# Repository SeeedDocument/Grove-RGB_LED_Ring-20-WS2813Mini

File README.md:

# Grove-RGB_LED_Ring-20-WS2813Mini

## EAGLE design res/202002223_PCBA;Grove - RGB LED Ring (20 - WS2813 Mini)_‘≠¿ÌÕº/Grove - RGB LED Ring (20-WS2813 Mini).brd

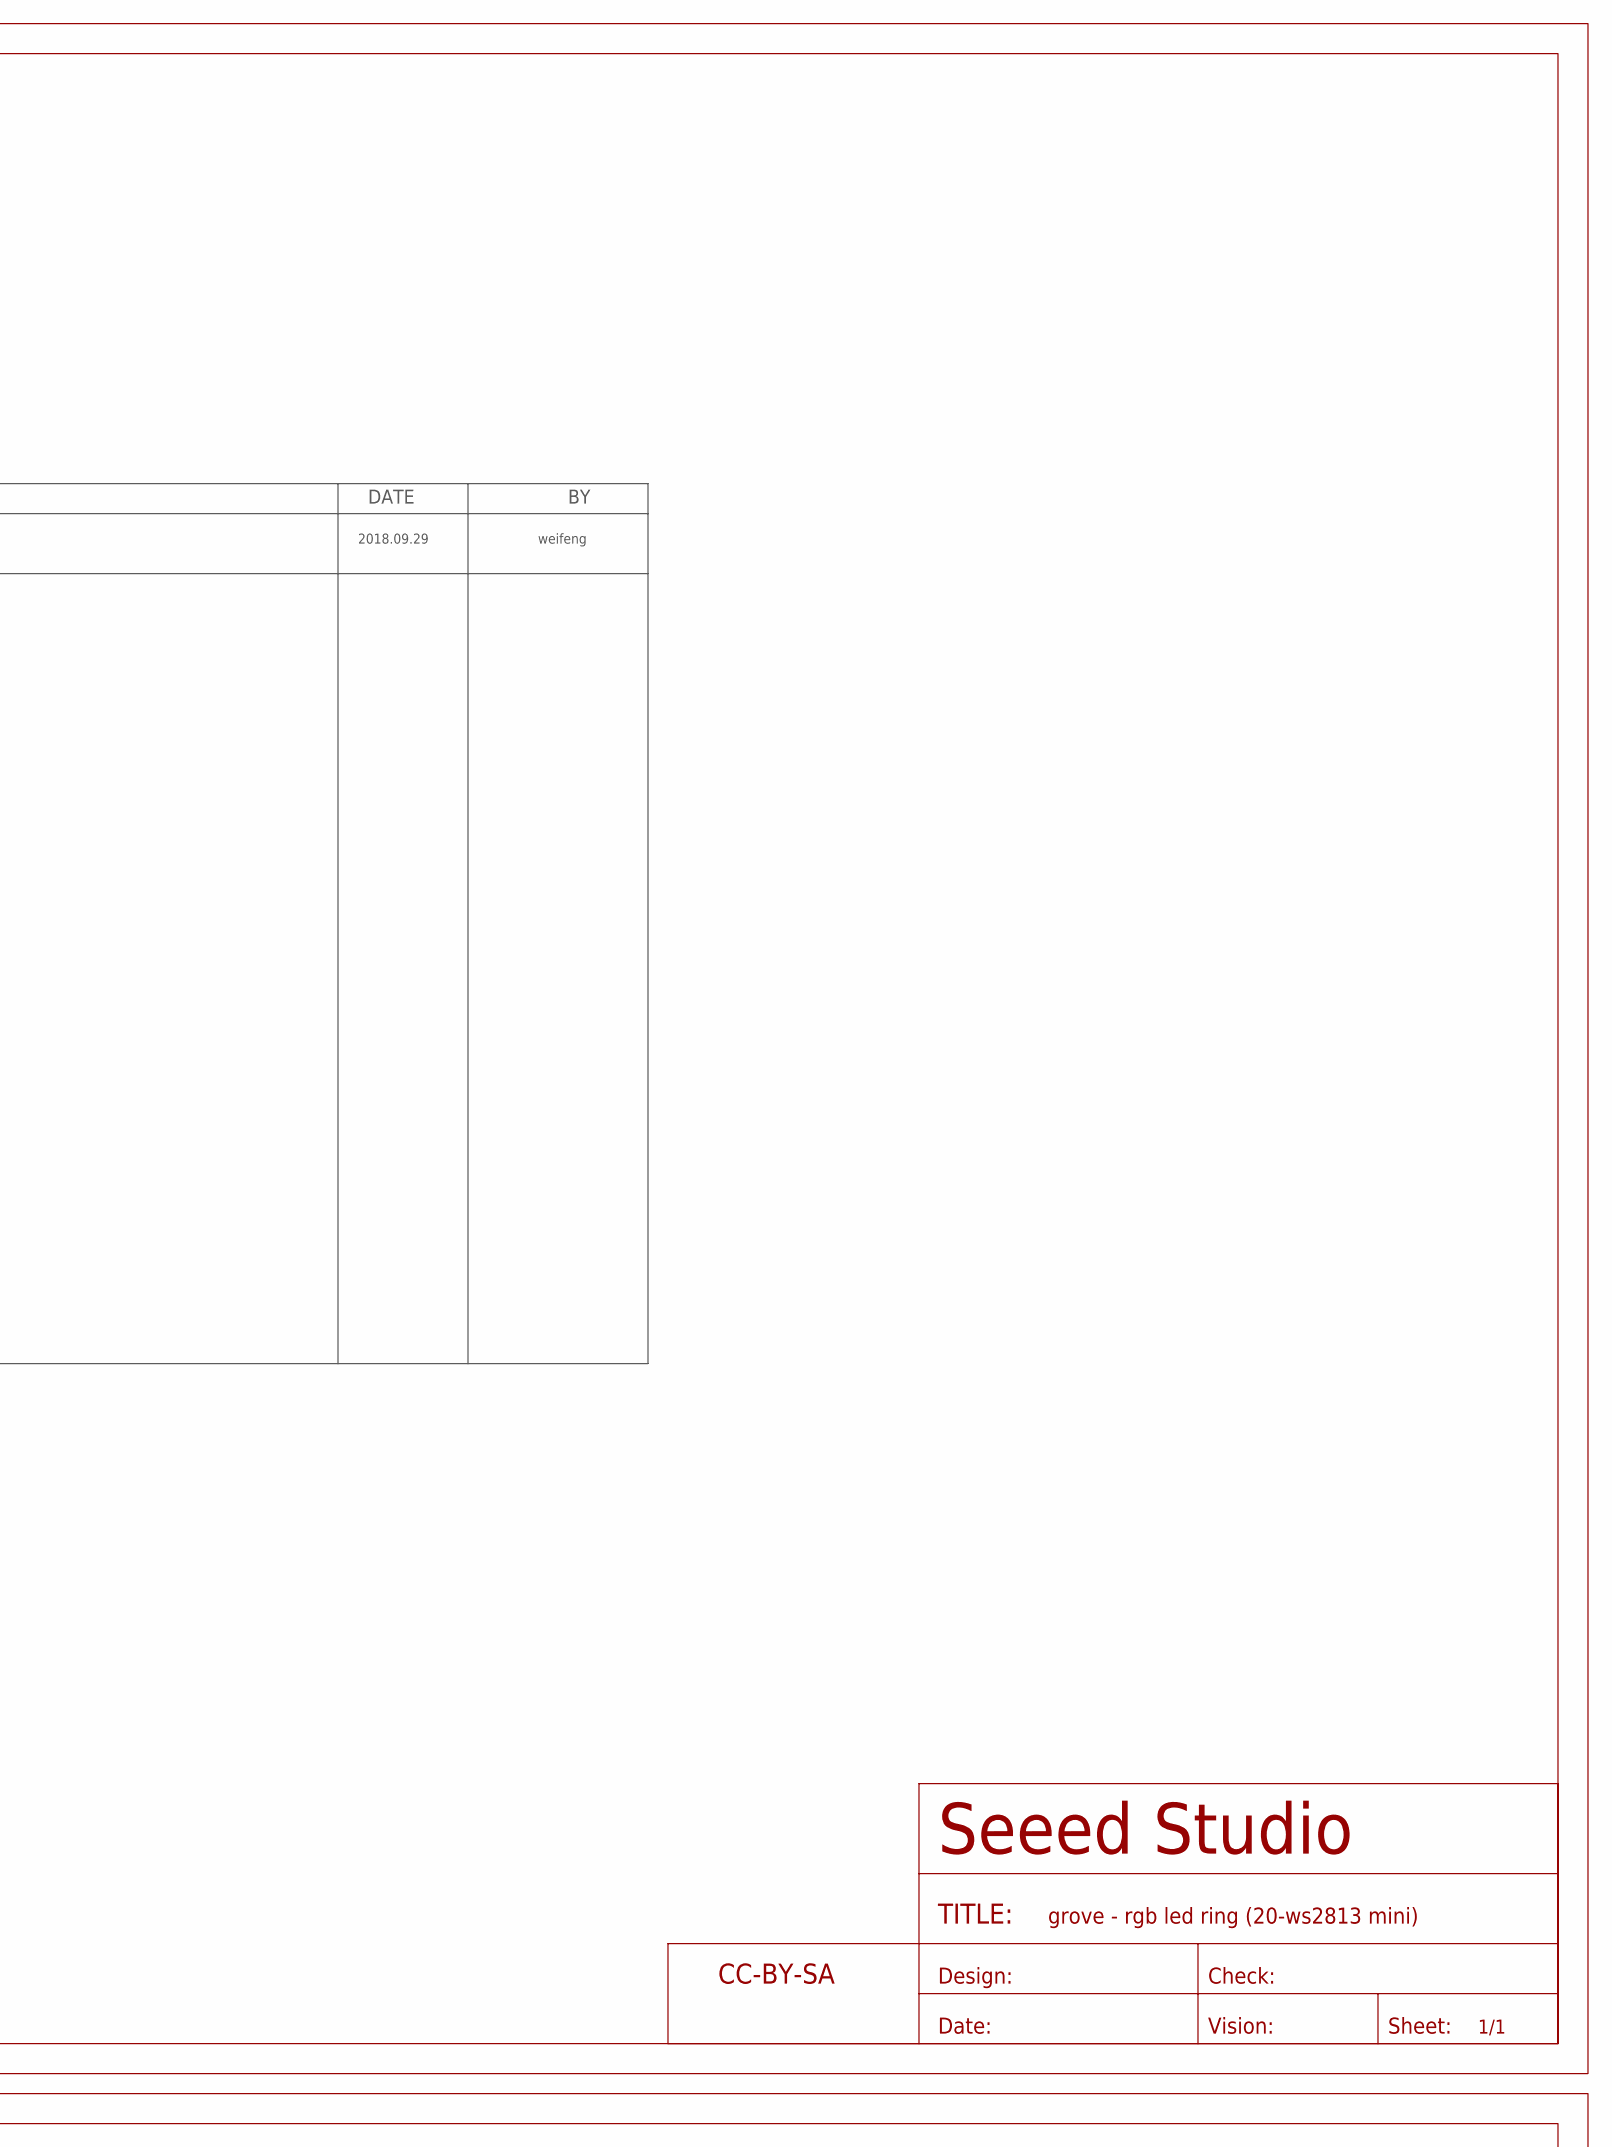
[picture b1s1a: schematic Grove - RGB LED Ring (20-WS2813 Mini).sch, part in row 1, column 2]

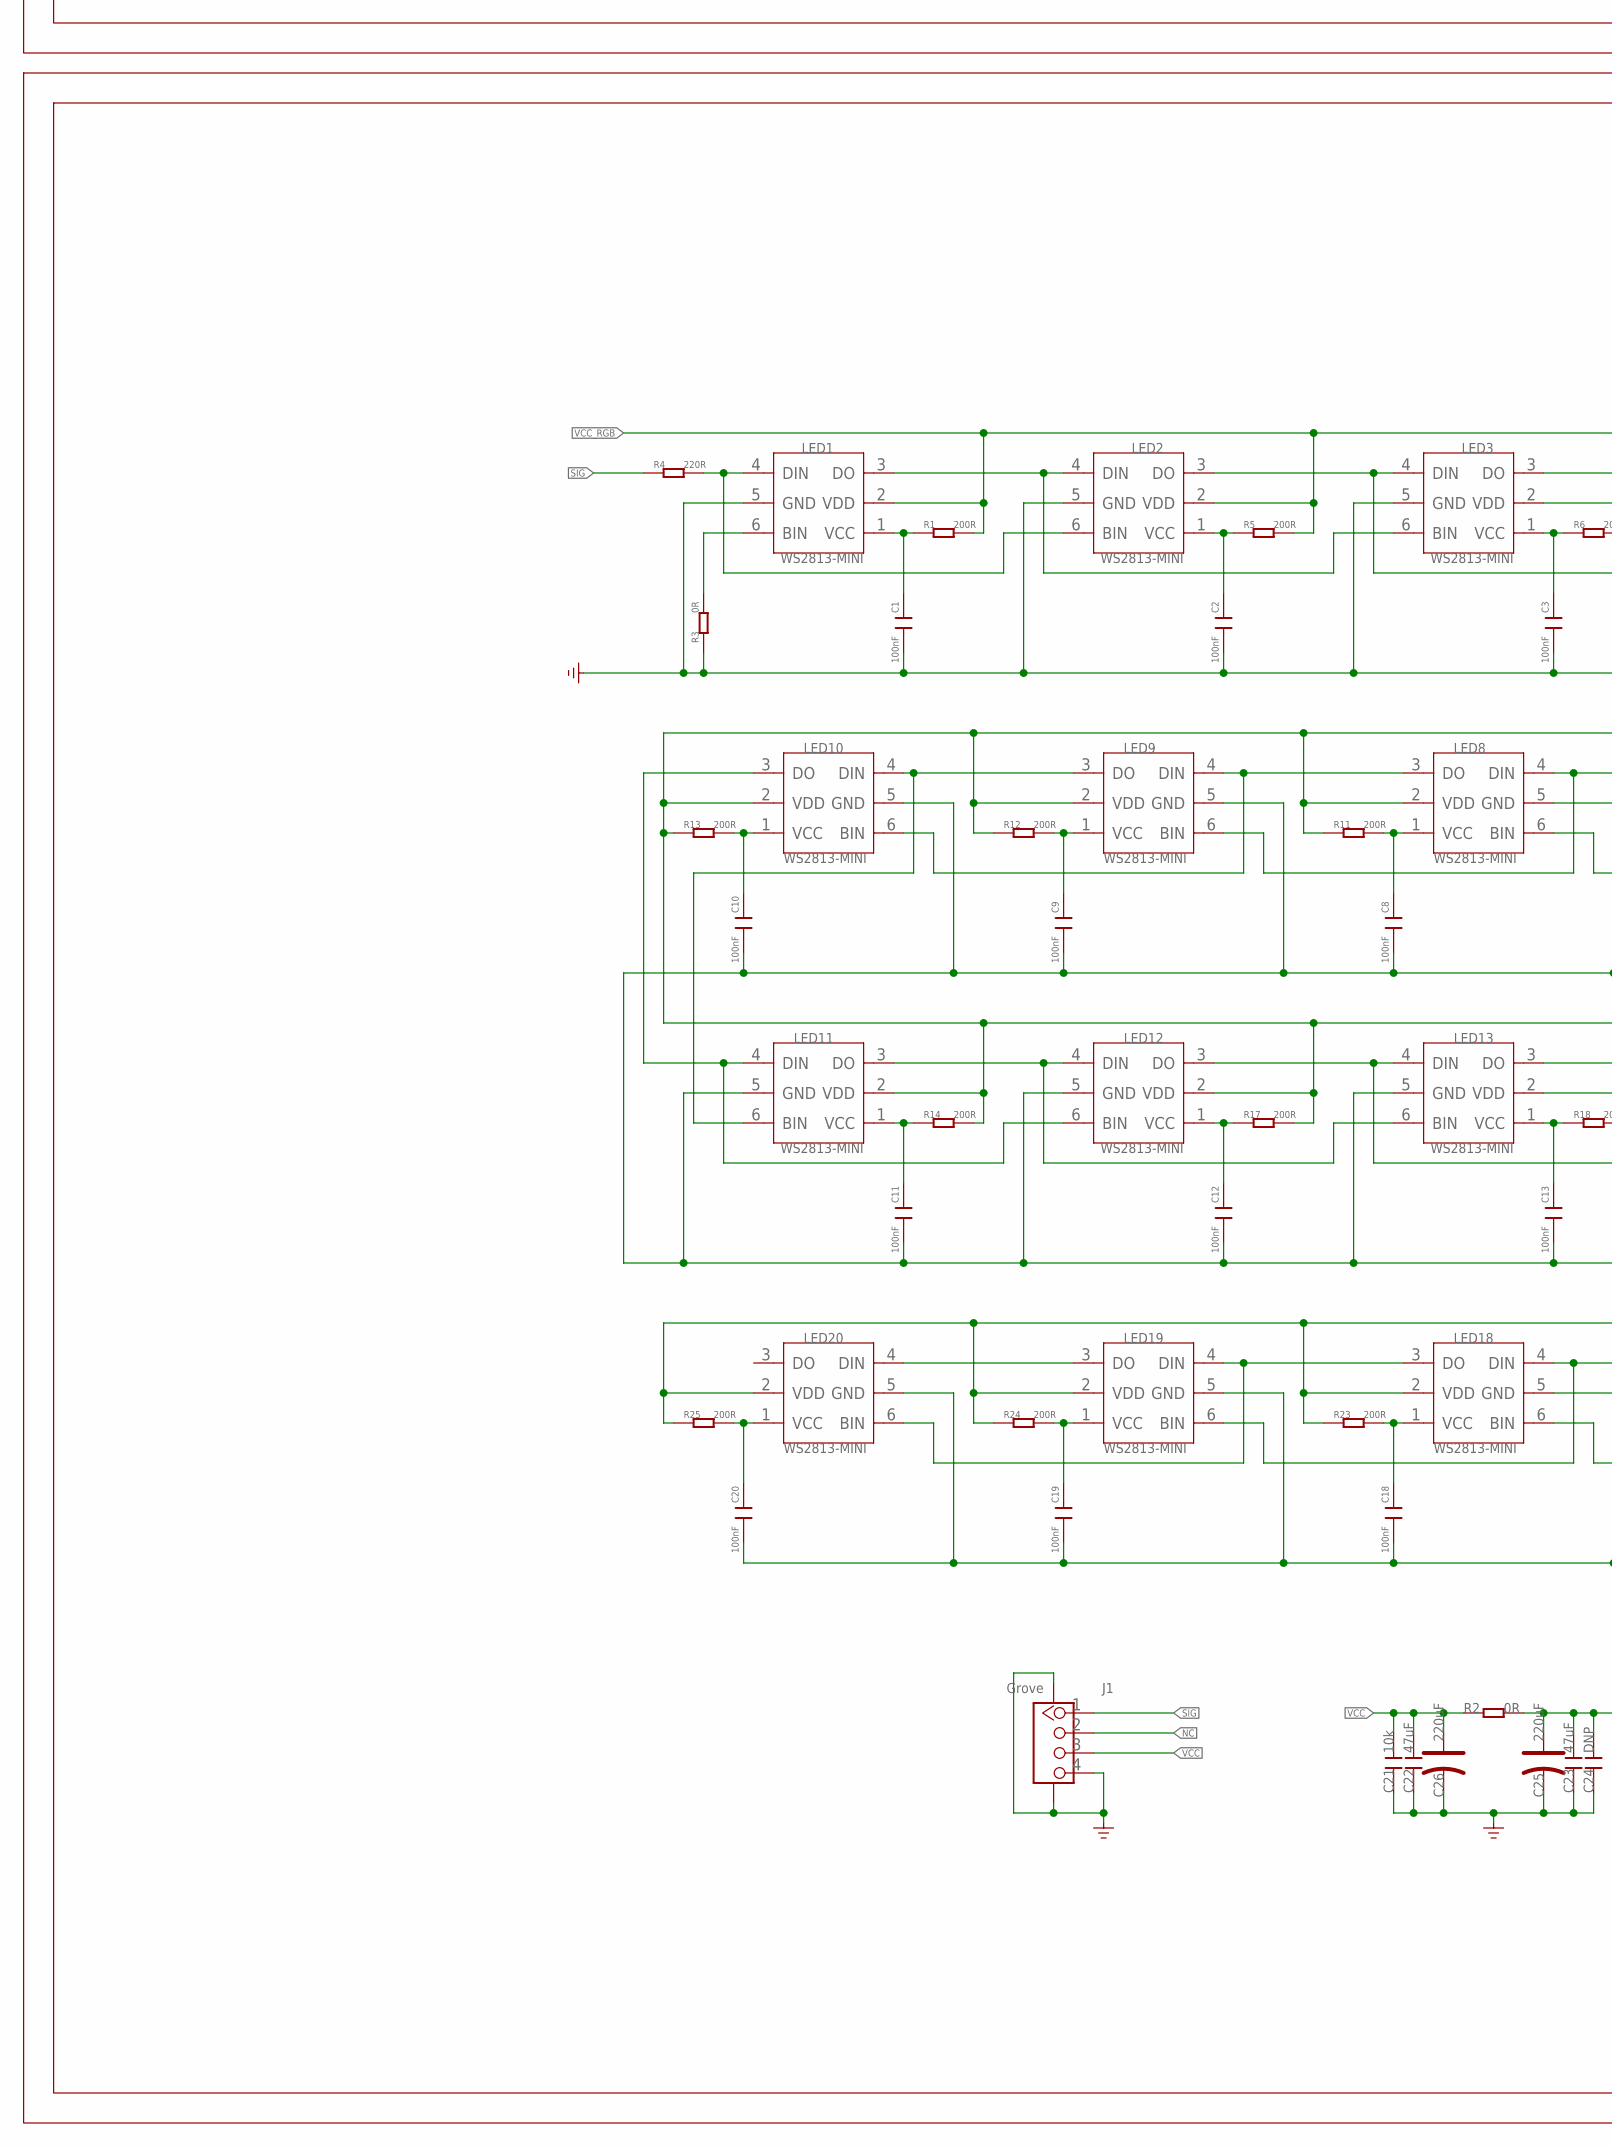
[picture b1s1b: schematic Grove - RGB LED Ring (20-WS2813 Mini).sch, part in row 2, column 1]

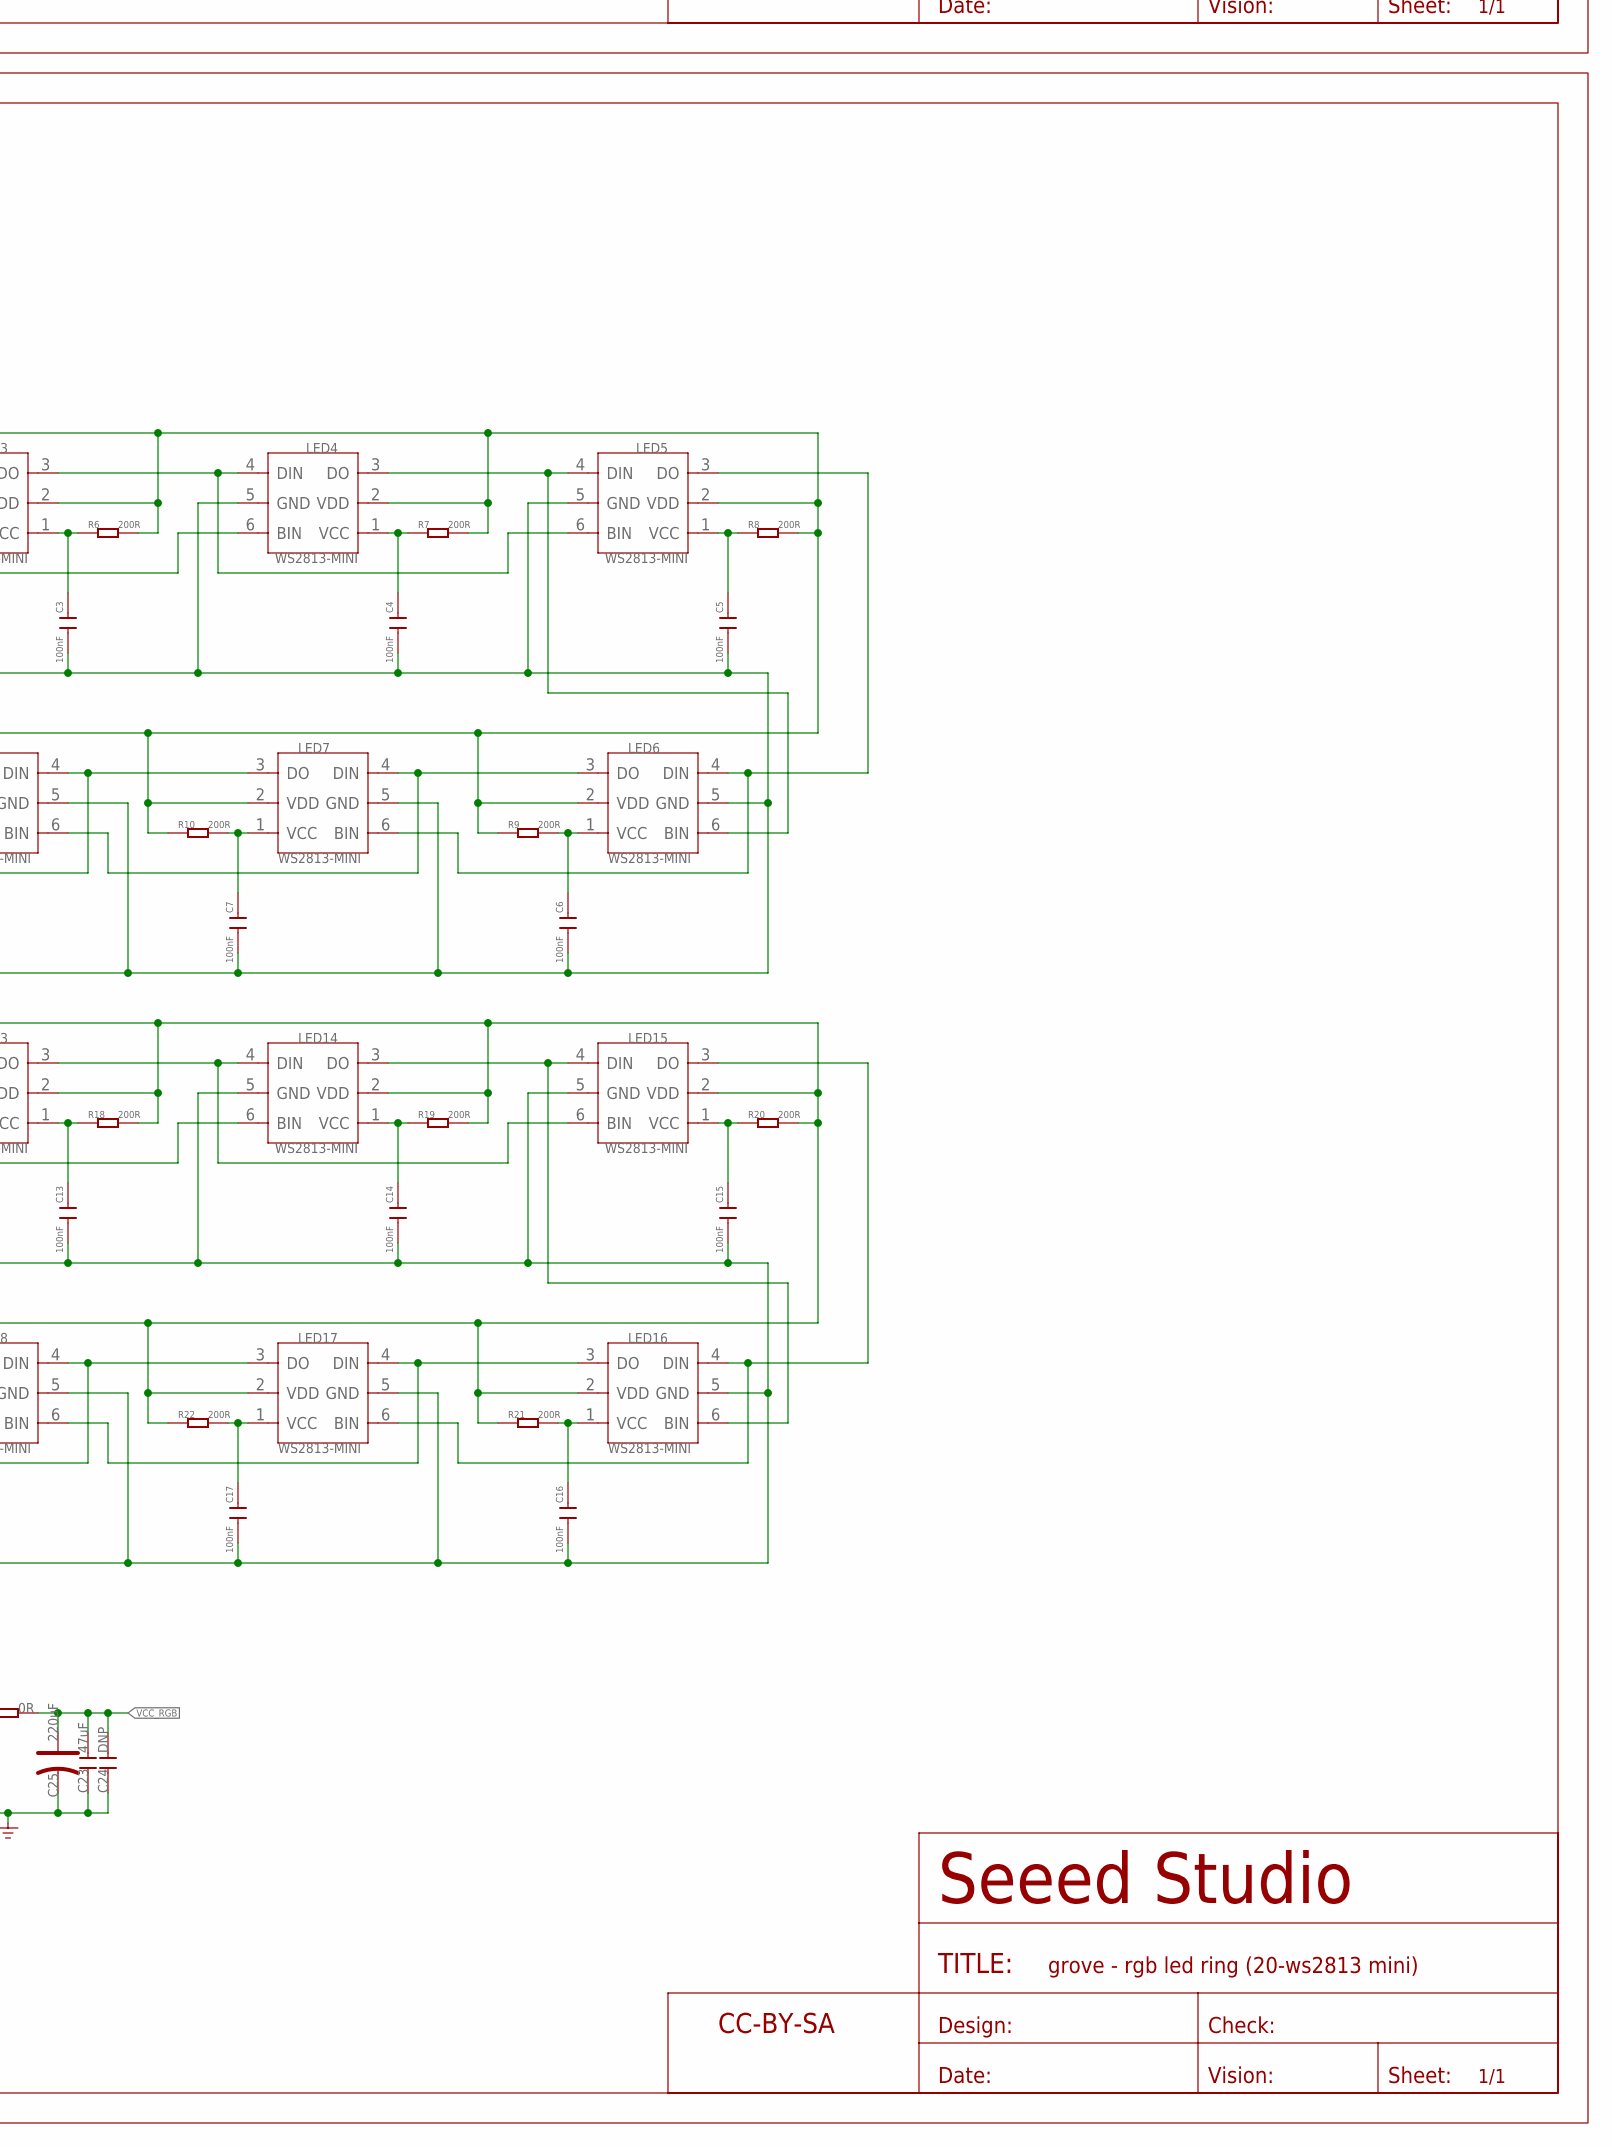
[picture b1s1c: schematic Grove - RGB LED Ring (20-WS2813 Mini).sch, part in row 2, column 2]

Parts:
C1, C2, C3, C4, C5, C6, C7, C8, C9, C10, C11, C12, C13, C14, C15, C16, C17, C18, C19, C20: 100nF; C0603
C21: 10k; C0603@1
C22, C23: 47uF; C0805
C24: DNP; C0603@1
C25, C26: 220uF; AVX-B
FR1, FR2: SEEEDSTUDIO-OPEN-SCH-FRAME-BIG; SEEEDSTUDIO-PCB-FRAME
J1: Grove; HW4-SMD-2.0
LED1, LED2, LED3, LED4, LED5, LED6, LED7, LED8, LED9, LED10, LED11, LED12, LED13, LED14, LED15, LED16, LED17, LED18, LED19, LED20: WS2813-MINI; LED6-1.1-3.5X3.5X0.95MM
R1, R5, R6, R7, R8, R9, R10, R11, R12, R13, R14, R17, R18, R19, R20, R21, R22, R23, R24, R25: 200R; R0603
R2: 0R; R0805
R3: 0R; R0603
R4: 220R; R0603

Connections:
GND: C1.1, C2.1, C3.1, C4.1, C5.1, C6.1, C7.1, C8.1, C9.1, C10.1, C11.1, C12.1, C13.1, C14.1, C15.1, C16.1, C17.1, C18.1, C19.1, C20.1, C21.1, C22.1, C23.1, C24.1, C25.-, C26.-, J1.4, J1.SS1, J1.SS2, LED1.5 (GND), LED2.5 (GND), LED3.5 (GND), LED4.5 (GND), LED5.5 (GND), LED6.5 (GND), LED7.5 (GND), LED8.5 (GND), LED9.5 (GND), LED10.5 (GND), LED11.5 (GND), LED12.5 (GND), LED13.5 (GND), LED14.5 (GND), LED15.5 (GND), LED16.5 (GND), LED17.5 (GND), LED18.5 (GND), LED19.5 (GND), LED20.5 (GND), R3.1
unnamed: C1.2, LED1.1 (VCC), R1.1
unnamed: LED2.3 (DO), LED3.4 (DIN), LED4.6 (BIN)
unnamed: C4.2, LED4.1 (VCC), R7.1
unnamed: LED1.6 (BIN), R3.2
unnamed: LED3.3 (DO), LED4.4 (DIN), LED5.6 (BIN)
unnamed: LED1.4 (DIN), LED2.6 (BIN), R4.2
unnamed: LED4.3 (DO), LED5.4 (DIN), LED6.6 (BIN)
unnamed: C5.2, LED5.1 (VCC), R8.1
unnamed: LED5.3 (DO), LED6.4 (DIN), LED7.6 (BIN)
unnamed: C2.2, LED2.1 (VCC), R5.1
unnamed: C6.2, LED6.1 (VCC), R9.2
unnamed: LED1.3 (DO), LED2.4 (DIN), LED3.6 (BIN)
unnamed: C3.2, LED3.1 (VCC), R6.1
unnamed: LED6.3 (DO), LED7.4 (DIN), LED8.6 (BIN)
unnamed: C7.2, LED7.1 (VCC), R10.2
unnamed: LED7.3 (DO), LED8.4 (DIN), LED9.6 (BIN)
unnamed: C8.2, LED8.1 (VCC), R11.2
unnamed: LED8.3 (DO), LED9.4 (DIN), LED10.6 (BIN)
unnamed: C9.2, LED9.1 (VCC), R12.2
unnamed: LED9.3 (DO), LED10.4 (DIN), LED11.6 (BIN)
unnamed: C10.2, LED10.1 (VCC), R13.2
unnamed: C11.2, LED11.1 (VCC), R14.1
unnamed: LED10.3 (DO), LED11.4 (DIN), LED12.6 (BIN)
unnamed: C12.2, LED12.1 (VCC), R17.1
unnamed: LED11.3 (DO), LED12.4 (DIN), LED13.6 (BIN)
unnamed: C13.2, LED13.1 (VCC), R18.1
unnamed: LED12.3 (DO), LED13.4 (DIN), LED14.6 (BIN)
unnamed: C14.2, LED14.1 (VCC), R19.1
unnamed: LED13.3 (DO), LED14.4 (DIN), LED15.6 (BIN)
unnamed: LED14.3 (DO), LED15.4 (DIN), LED16.6 (BIN)
unnamed: C15.2, LED15.1 (VCC), R20.1
unnamed: LED15.3 (DO), LED16.4 (DIN), LED17.6 (BIN)
unnamed: C16.2, LED16.1 (VCC), R21.2
unnamed: LED16.3 (DO), LED17.4 (DIN), LED18.6 (BIN)
unnamed: C17.2, LED17.1 (VCC), R22.2
unnamed: LED17.3 (DO), LED18.4 (DIN), LED19.6 (BIN)
unnamed: C18.2, LED18.1 (VCC), R23.2
unnamed: LED18.3 (DO), LED19.4 (DIN), LED20.6 (BIN)
unnamed: C19.2, LED19.1 (VCC), R24.2
unnamed: LED19.3 (DO), LED20.4 (DIN)
unnamed: C20.2, LED20.1 (VCC), R25.2
NC: J1.2
SIG: J1.1, R4.1
VCC: C21.2, C22.2, C26.+, J1.3, R2.1
VCC_RGB: C23.2, C24.2, C25.+, LED1.2 (VDD), LED2.2 (VDD), LED3.2 (VDD), LED4.2 (VDD), LED5.2 (VDD), LED6.2 (VDD), LED7.2 (VDD), LED8.2 (VDD), LED9.2 (VDD), LED10.2 (VDD), LED11.2 (VDD), LED12.2 (VDD), LED13.2 (VDD), LED14.2 (VDD), LED15.2 (VDD), LED16.2 (VDD), LED17.2 (VDD), LED18.2 (VDD), LED19.2 (VDD), LED20.2 (VDD), R1.2, R2.2, R5.2, R6.2, R7.2, R8.2, R9.1, R10.1, R11.1, R12.1, R13.1, R14.2, R17.2, R18.2, R19.2, R20.2, R21.1, R22.1, R23.1, R24.1, R25.1

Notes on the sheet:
v1.0
Initial Version
2018.09.29
weifeng

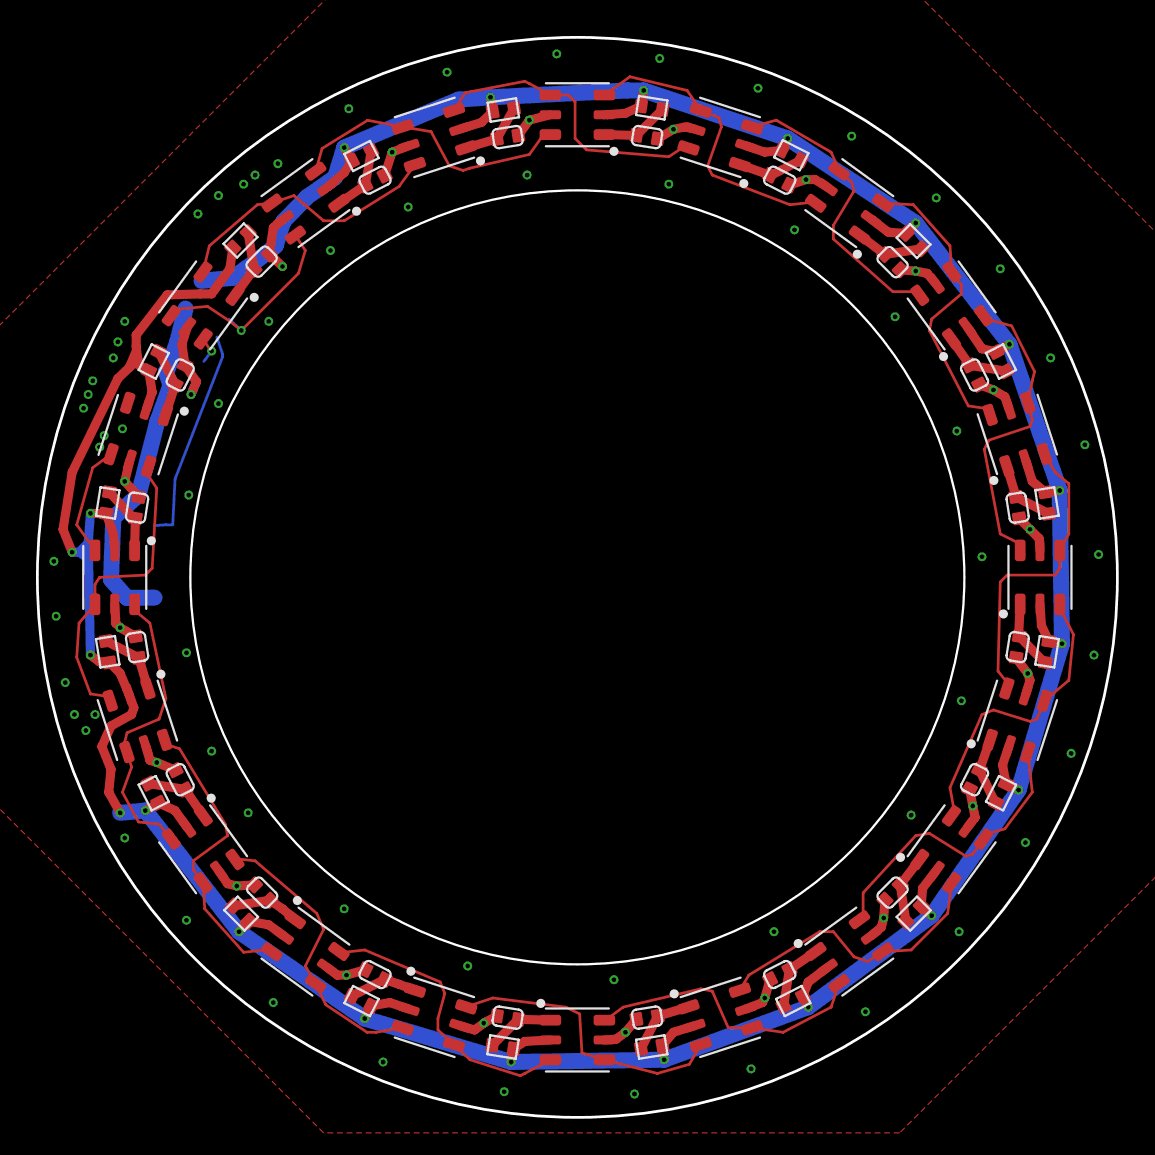
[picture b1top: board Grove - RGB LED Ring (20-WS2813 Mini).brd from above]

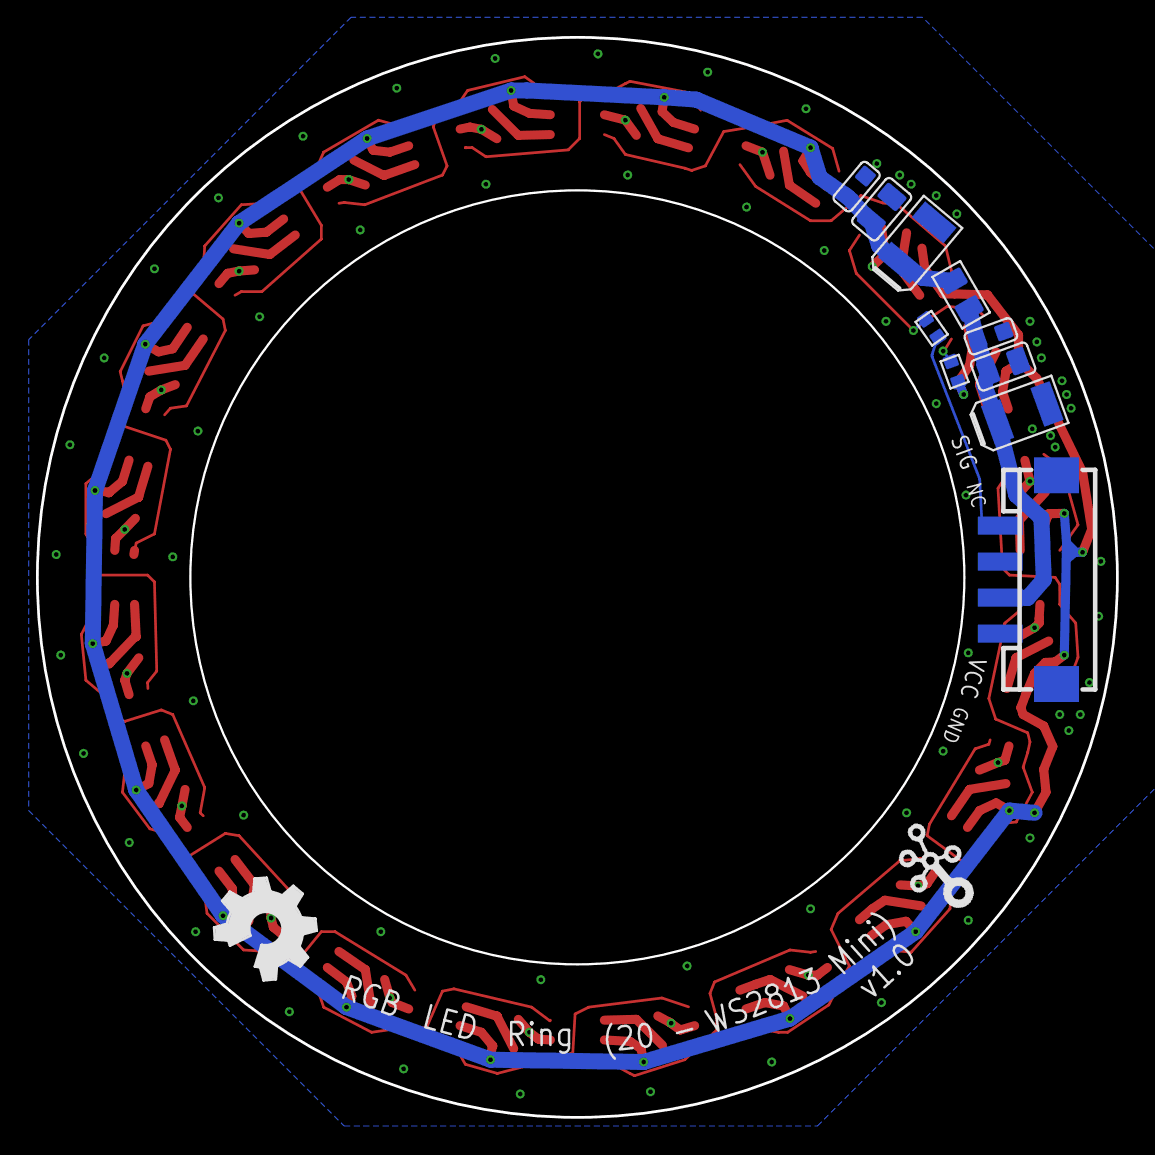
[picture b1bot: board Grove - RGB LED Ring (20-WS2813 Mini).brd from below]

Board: 2 copper layers, 60.0 x 60.0 mm, 74 parts (12 on the bottom side), 45 nets.

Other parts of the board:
U$7: GROVE-SILK-SMALL
U$8: OSHW_FILLX200_NOTEXT

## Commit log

2018-12-06 chinese pin map

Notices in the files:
parts and their libraries:
moudle-new: This work is licensed under the Creative Commons Attribution 4.0 International License.
To view a copy of this license,visit:
http://creativecommons.org/licenses/by-sa/4.0
moudle-new: CC-BY-SA
